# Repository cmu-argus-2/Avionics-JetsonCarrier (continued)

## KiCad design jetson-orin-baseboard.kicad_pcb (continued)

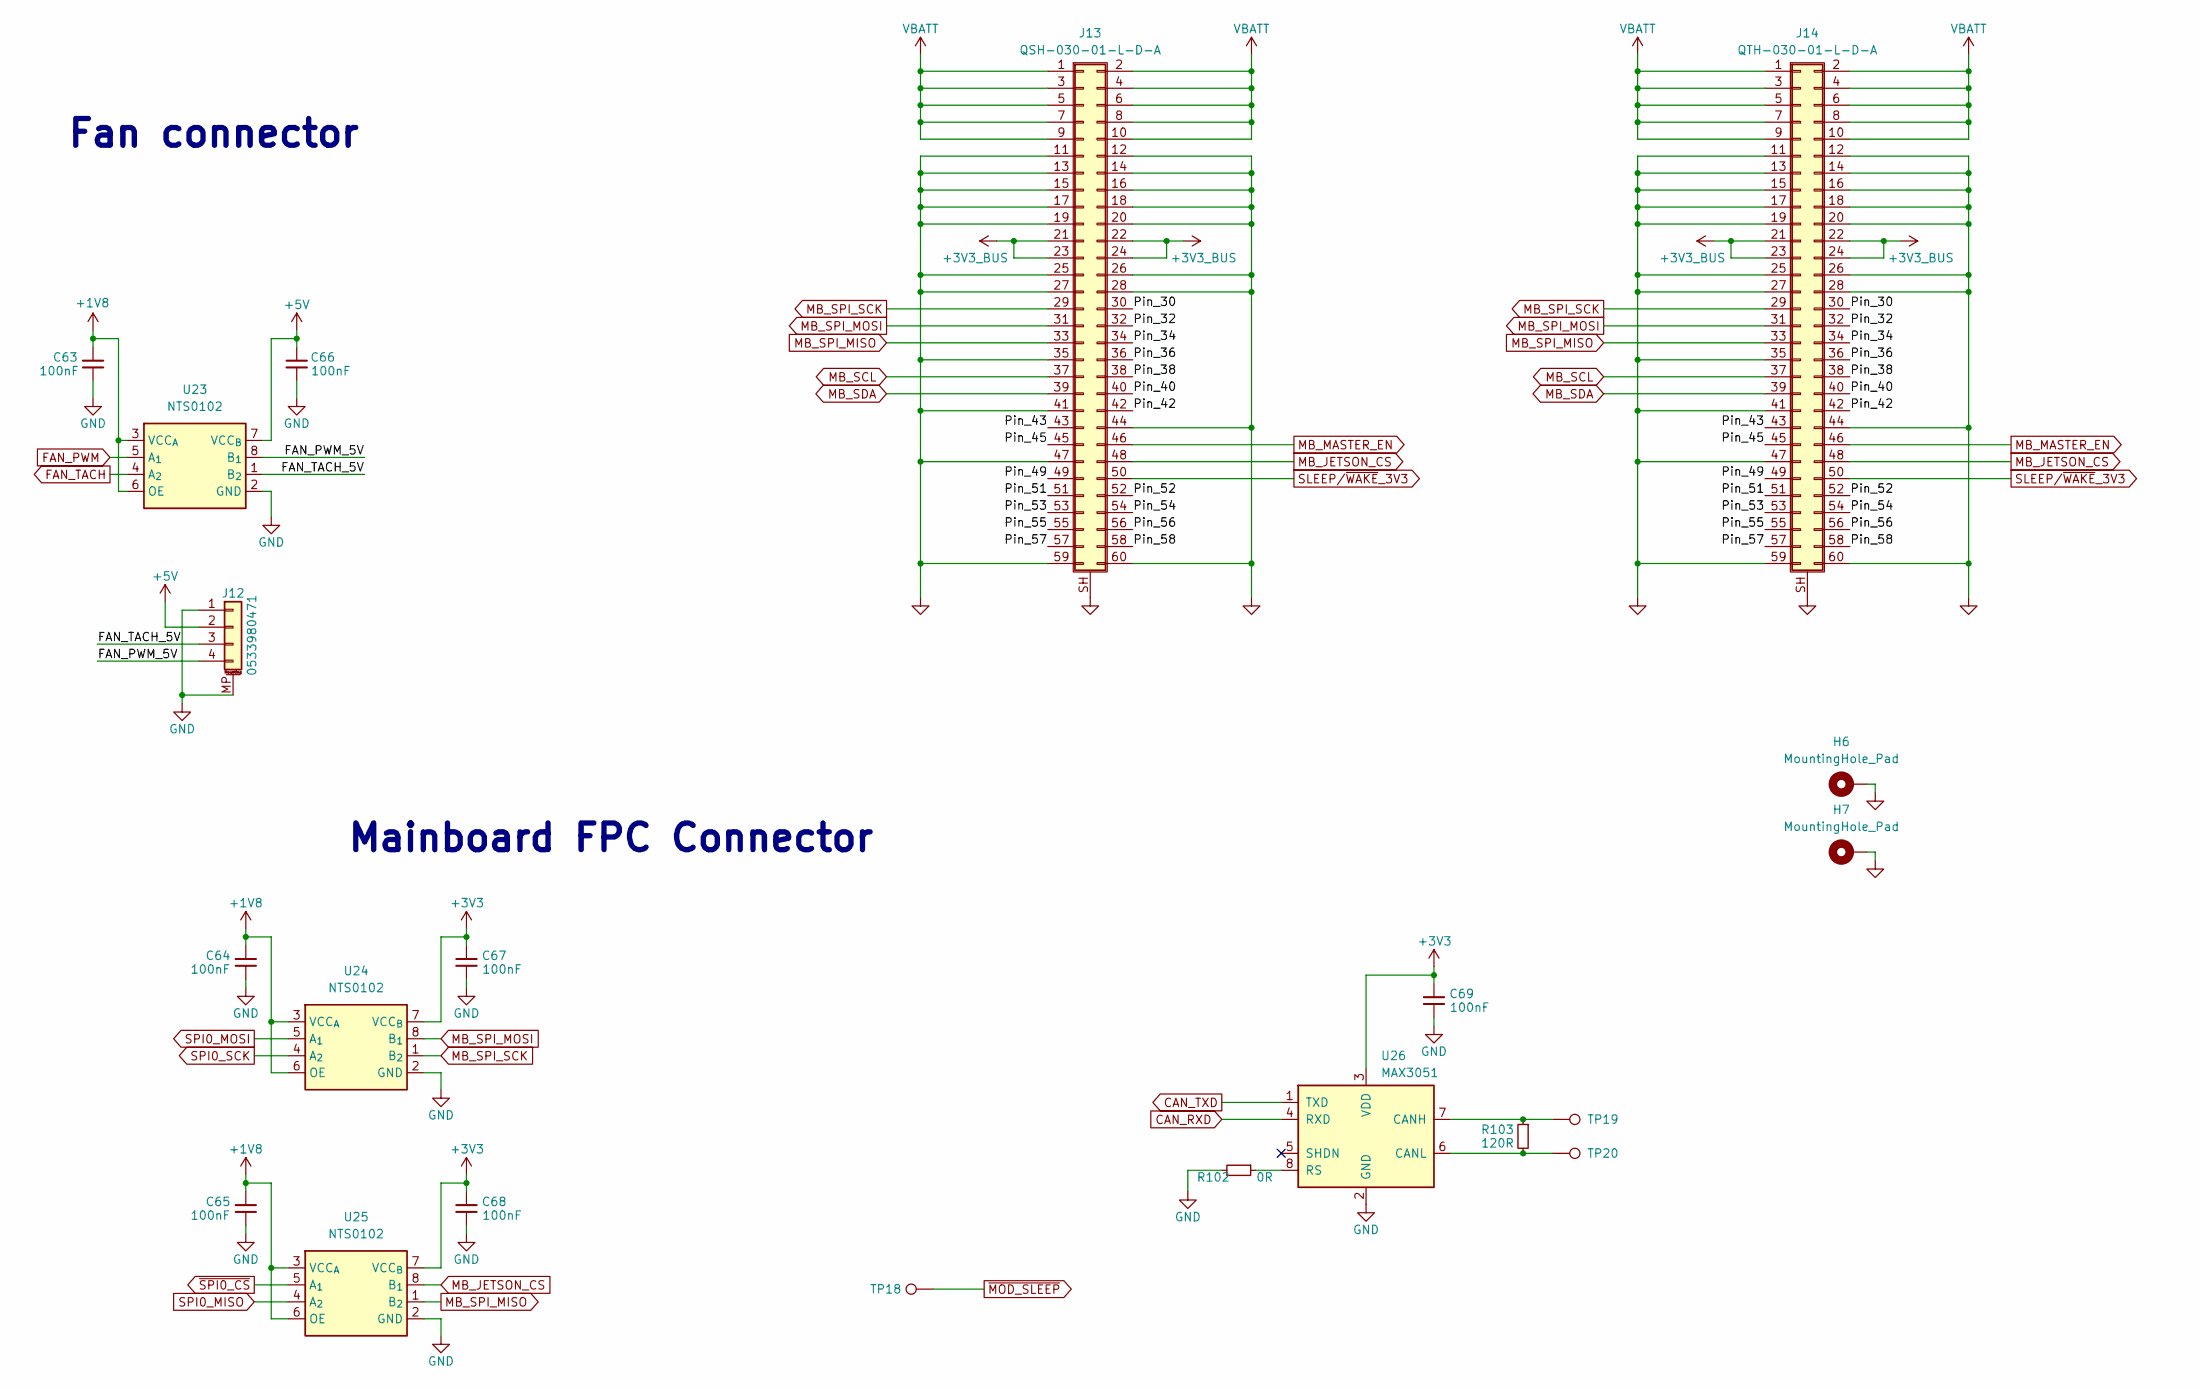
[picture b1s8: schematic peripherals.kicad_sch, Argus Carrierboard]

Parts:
C63, C64, C65, C66, C67, C68, C69: 100nF; C_0603_1608Metric; MPN C307348; LCSC C14663
H6, H7: MountingHole_Pad; MountingHole_2.5mm_Pad_Via
J12: 0533980471; Molex_PicoBlade_53398-0471_1x04-1MP_P1.25mm_Vertical; MPN C225106; LCSC C17617036
J13: QSH-030-01-L-D-A; SAMTEC_QSH-030-01-L-D-A; LCSC C2909821
J14: QTH-030-01-L-D-A; SAMTEC-QTH-030-01-X-D-A; LCSC C2843756
R102: 0R; R_0603_1608Metric; MPN C190119; LCSC C21189
R103: 120R; R_0603_1608Metric; MPN C71617; LCSC C22787
TP18, TP19, TP20: TP_0.75mm_SMD; TestPoint_Pad_D1.0mm
U23, U24, U25: NTS0102; NXP_XSON-8; MPN NTS0102GT; LCSC C2687851
U26: MAX3051; SOT-23-8; LCSC C112005

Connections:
+1V8: C63.1, C64.1, C65.1, U23.3 (VCC_{A}), U23.6 (OE), U24.3 (VCC_{A}), U24.6 (OE), U25.3 (VCC_{A}), U25.6 (OE); also elsewhere on the board
+3V3: C67.1, C68.1, C69.1, U24.7 (VCC_{B}), U25.7 (VCC_{B}), U26.3 (VDD); also elsewhere on the board
+3V3_BUS: J13.21, J13.22, J13.23, J13.24, J14.21, J14.22, J14.23, J14.24; also elsewhere on the board
+5V: C66.1, J12.2, U23.7 (VCC_{B}); also elsewhere on the board
/Peripherals/FAN_PWM_5V: J12.4, U23.8 (B_{1})
/Peripherals/FAN_TACH_5V: J12.3, U23.1 (B_{2})
/Peripherals/Pin_30: J13.30, J14.30
/Peripherals/Pin_32: J13.32, J14.32
/Peripherals/Pin_34: J13.34, J14.34
/Peripherals/Pin_36: J13.36, J14.36
/Peripherals/Pin_38: J13.38, J14.38
/Peripherals/Pin_40: J13.40, J14.40
/Peripherals/Pin_42: J13.42, J14.42
/Peripherals/Pin_43: J13.43, J14.43
/Peripherals/Pin_45: J13.45, J14.45
/Peripherals/Pin_49: J13.49, J14.49
/Peripherals/Pin_51: J13.51, J14.51
/Peripherals/Pin_52: J13.52, J14.52
/Peripherals/Pin_53: J13.53, J14.53
/Peripherals/Pin_54: J13.54, J14.54
/Peripherals/Pin_55: J13.55, J14.55
/Peripherals/Pin_56: J13.56, J14.56
/Peripherals/Pin_57: J13.57, J14.57
/Peripherals/Pin_58: J13.58, J14.58
CAN_RXD: U26.4 (RXD); also elsewhere on the board
CAN_TXD: U26.1 (TXD); also elsewhere on the board
FAN_PWM: U23.5 (A_{1}); also elsewhere on the board
FAN_TACH: U23.4 (A_{2}); also elsewhere on the board
GND: C63.2, C64.2, C65.2, C66.2, C67.2, C68.2, C69.2, H6.1 (1_1), H7.1 (1_1), J12.1, J12.MP (MountPin), J13.11, J13.12, J13.13, J13.14, J13.15, J13.16, J13.17, J13.18, J13.19, J13.20, J13.25, J13.26, J13.27, J13.28, J13.35, J13.41, J13.44, J13.47, J13.59, J13.60, J13.SH (Shield), J14.11, J14.12, J14.13, J14.14, J14.15, J14.16, J14.17, J14.18, J14.19, J14.20, J14.25, J14.26, J14.27, J14.28, J14.35, J14.41, J14.44, J14.47, J14.59, J14.60, J14.SH (Shield), R102.2, U23.2 (GND), U24.2 (GND), U25.2 (GND), U26.2 (GND); also elsewhere on the board
MB_JETSON_CS: J13.48, J14.48, U25.8 (B_{1})
MB_MASTER_EN: J13.46, J14.46; also elsewhere on the board
MB_SCL: J13.37, J14.37; also elsewhere on the board
MB_SDA: J13.39, J14.39; also elsewhere on the board
MB_SPI_MISO: J13.33, J14.33, U25.1 (B_{2})
MB_SPI_MOSI: J13.31, J14.31, U24.8 (B_{1})
MB_SPI_SCK: J13.29, J14.29, U24.1 (B_{2})
unnamed: R103.1, TP19.1 (1_1), U26.7 (CANH)
unnamed: R103.2, TP20.1 (1_1), U26.6 (CANL)
unnamed: R102.1, U26.8 (RS)
SLEEP/~WAKE_3V3: J13.50, J14.50; also elsewhere on the board
SPI0_MISO: U25.4 (A_{2}); also elsewhere on the board
SPI0_MOSI: U24.5 (A_{1}); also elsewhere on the board
SPI0_SCK: U24.4 (A_{2}); also elsewhere on the board
VBATT: J13.1, J13.2, J13.3, J13.4, J13.5, J13.6, J13.7, J13.8, J13.9, J13.10, J14.1, J14.2, J14.3, J14.4, J14.5, J14.6, J14.7, J14.8, J14.9, J14.10; also elsewhere on the board
~MOD_SLEEP: TP18.1 (1_1); also elsewhere on the board
~SPI0_CS: U25.5 (A_{1}); also elsewhere on the board

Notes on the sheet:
Fan connector
Mainboard FPC Connector

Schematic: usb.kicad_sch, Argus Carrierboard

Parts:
C23, C25: 10uF; C_0603_1608Metric; MPN C697423; LCSC C96446
C24, C26, C27, C31: 100nF; C_0603_1608Metric; MPN C307348; LCSC C14663
C28, C30: 47pF; C_0402_1005Metric; MPN C126511; LCSC C1567
C29: 1uF; C_0603_1608Metric; MPN C2214844; LCSC C15849
D4, D5: LED_G_0603_LTST-C190GKT; LED_0603_1608Metric; MPN C2909774; LCSC C2290
D6: LED_G_0603_LTST-C190GKT; LED_0603_1608Metric; MPN C2909774; LCSC C12065
D7: ESD9X5.0ST5G; D_SOD-923; MPN C87910; LCSC C87910
J3: USB_C_Receptacle_USB2.0_16P; USB_C_Receptacle_GCT_USB4105-xx-A_16P_TopMnt_Horizontal; LCSC C3020560
R22: 10k; R_0603_1608Metric; MPN C2479067; LCSC C25804
R23, R24: 0R; R_0402_1005Metric; MPN C190119; LCSC C17168
R25, R26: 3k3; R_0603_1608Metric; MPN C844928; LCSC C22978
R27: 4k7; R_0603_1608Metric; MPN C844931; LCSC C23162
R28, R29: 27R; R_0603_1608Metric; MPN C844545; LCSC C227752
R30, R31: 5k1; R_0603_1608Metric; MPN C490833; LCSC C23186
TP6, TP7: TP_0.75mm_SMD; TestPoint_Pad_D1.0mm
U2: NCP730BMT330; WSON-6-1EP_2x2mm_P0.65mm; MPN C892821; LCSC C892821
U3: FT230X; QFN-16-1EP_4x4mm_P0.65mm_EP2.1x2.1mm; MPN C128629; LCSC C128629
U4: TPD4E05U06QDQARQ1; USON-10_TEX; MPN C81353; LCSC C81353

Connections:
/Debug/FTDI_3V3: C23.2, C24.2, C26.2, R22.2, R25.2, R26.1, U2.1 (V_{OUT}), U3.1 (V_{CCIO}), U3.8 (3V3_{OUT}), U3.10 (V_{CC})
/Debug/FTDI_CBUS0: TP6.1 (1_1), U3.12 (CBUS0)
/Debug/FTDI_CBUS3: TP7.1 (1_1), U3.14 (CBUS3)
/Debug/FTDI_LED_RX: D4.1 (K), U3.11 (CBUS1)
/Debug/FTDI_LED_TX: D5.1 (K), U3.5 (CBUS2)
/Debug/USBC3_CC1: J3.A5 (CC1), R30.1, U4.4, U4.7
/Debug/USBC3_CC2: J3.B5 (CC2), R31.1, U4.5, U4.6
/Debug/USBC3_D_N: C28.1, J3.A7 (D-), J3.B7 (D-), R28.1, U4.1, U4.10
/Debug/USBC3_D_P: C30.2, J3.A6 (D+), J3.B6 (D+), R29.1, U4.2, U4.9
/Debug/USBC3_VBUS: C25.2, C29.2, C31.2, D7.1 (K), J3.A4 (VBUS), J3.A9 (VBUS), J3.B4 (VBUS), J3.B9 (VBUS), R27.1, U2.4 (EN), U2.6 (V_{IN})
/Debug/USB_FTDI_N: R28.2, U3.7 (D-)
/Debug/USB_FTDI_P: R29.2, U3.6 (D+)
DEBUG_RXD: R23.2; also elsewhere on the board
DEBUG_TXD: R24.2; also elsewhere on the board
GND: C23.1, C24.1, C25.1, C26.1, C27.2, C28.2, C29.1, C30.1, C31.1, D6.1 (K), D7.2 (A), J3.A1 (GND), J3.A12 (GND), J3.B1 (GND), J3.B12 (GND), J3.SH (SHIELD), R30.2, R31.2, U2.3 (GND), U2.5 (PG), U2.7 (GND), U3.3 (GND), U3.13 (GND), U3.17 (GND), U4.3, U4.8; also elsewhere on the board
unnamed: D4.2 (A), R25.1
unnamed: D5.2 (A), R26.2
unnamed: D6.2 (A), R27.2
unnamed: R24.1, U3.2 (RXD)
unnamed: R23.1, U3.15 (TXD)
unnamed: C27.1, R22.1, U3.9 (~RESET)

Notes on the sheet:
USBC3
USB-UART Bridge
Debug USB-C 3

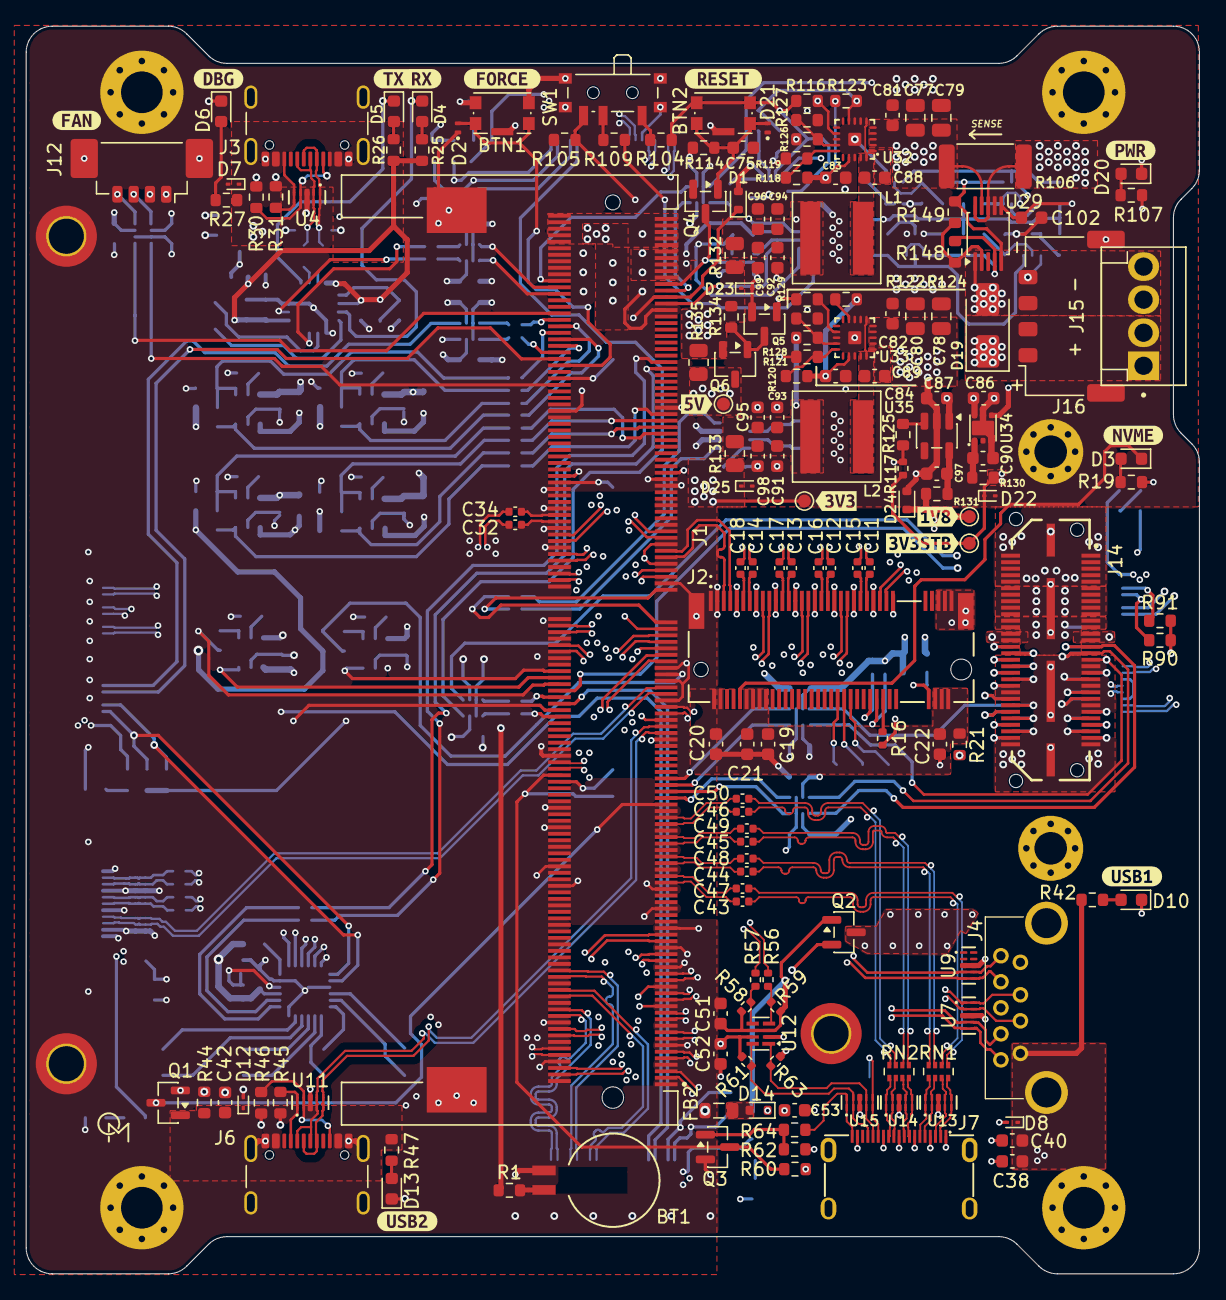
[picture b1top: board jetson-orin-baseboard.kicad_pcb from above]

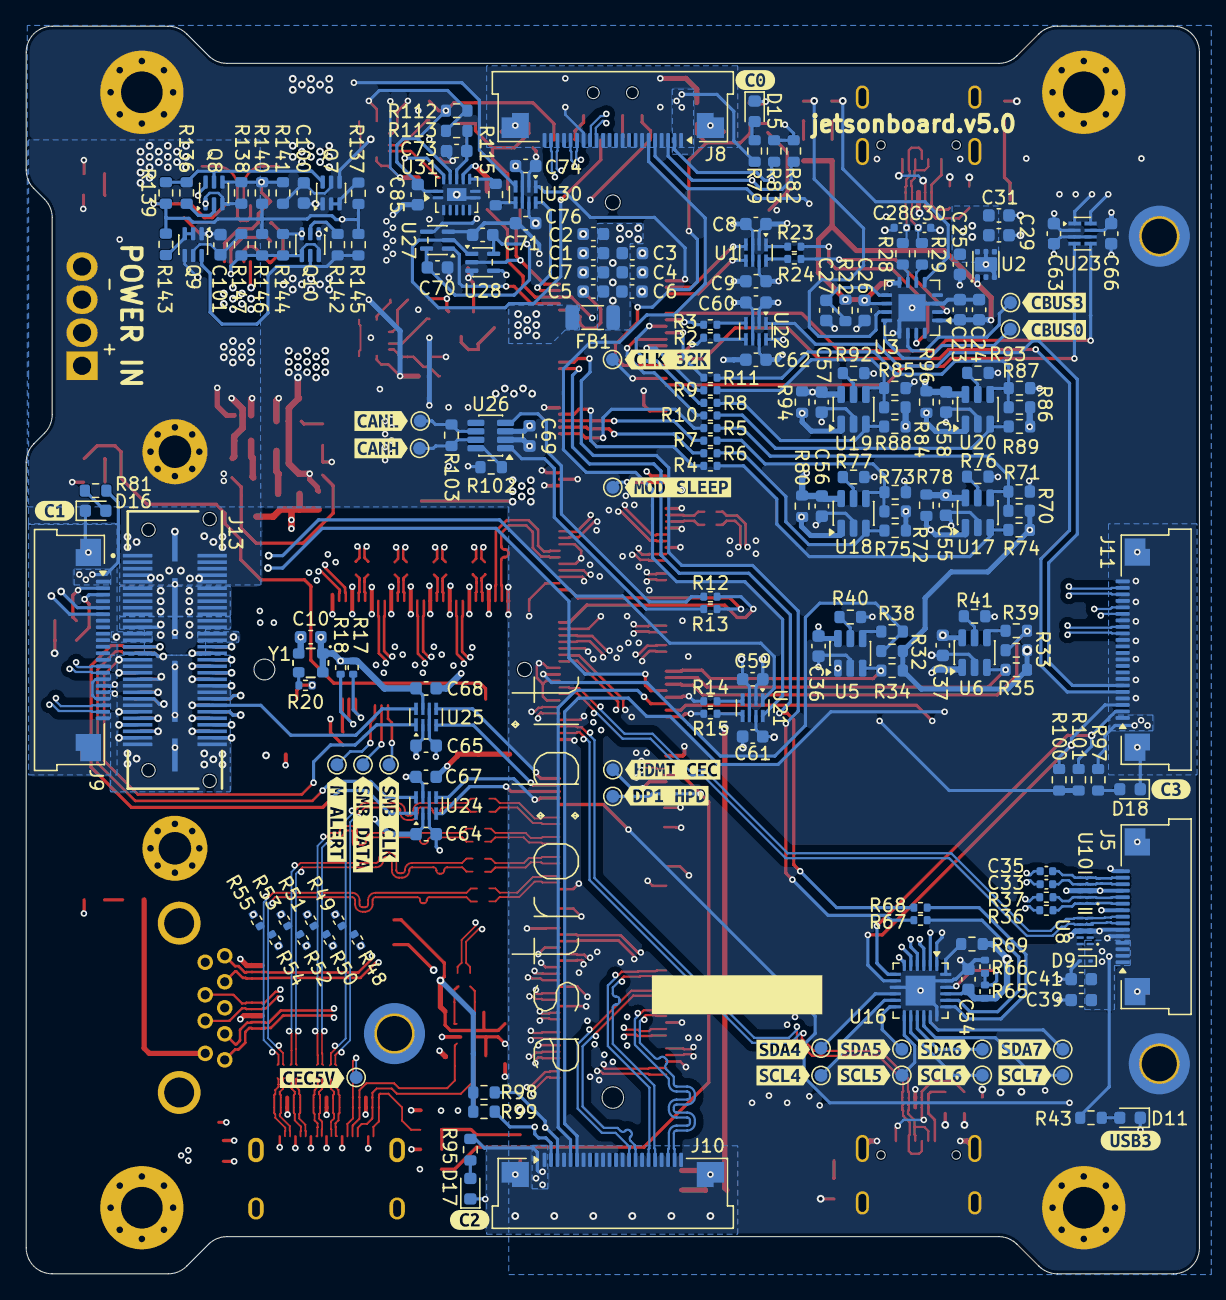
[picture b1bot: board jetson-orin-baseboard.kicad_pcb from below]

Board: 8 copper layers, 90.2 x 95.9 mm, 414 parts (227 on the bottom side), 325 nets.

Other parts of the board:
C100, C101: 10n; C_0603_1608Metric
Q7, Q9: NX3008NBKS; SOT-363_SC-70-6
Q8, Q10: MBT2222ADW1T1; SOT-363_SC-70-6
R136, R142: 680R; R_0603_1608Metric
R137, R143: 100k; R_0603_1608Metric
R138, R144: 0R; R_0603_1608Metric
R139, R140, R145, R146: 10k; R_0603_1608Metric
R141, R147: 200k; R_0603_1608Metric
kibuzzard-6AA4CB0A: G***; kibuzzard-6AA4CB0A
kibuzzard-6AA4CB7C: G***; kibuzzard-6AA4CB7C
kibuzzard-6AA4CB93: G***; kibuzzard-6AA4CB93
kibuzzard-6AA4CBA6: G***; kibuzzard-6AA4CBA6
kibuzzard-6AA4CCDD: G***; kibuzzard-6AA4CCDD
kibuzzard-6AA4CCE8: G***; kibuzzard-6AA4CCE8
kibuzzard-6AA4CCF3: G***; kibuzzard-6AA4CCF3
kibuzzard-6AA4CCFD: G***; kibuzzard-6AA4CCFD
kibuzzard-6AA4D0D5: G***; kibuzzard-6AA4D0D5
kibuzzard-6AA4D0E1: G***; kibuzzard-6AA4D0E1
kibuzzard-6AA4D3A3: G***; kibuzzard-6AA4D3A3
kibuzzard-6AA4D3AB: G***; kibuzzard-6AA4D3AB
kibuzzard-6AA4D4B3: G***; kibuzzard-6AA4D4B3
kibuzzard-6AA4D4C2: G***; kibuzzard-6AA4D4C2
kibuzzard-6AA4D4DE: G***; kibuzzard-6AA4D4DE
kibuzzard-6AA4D12B: G***; kibuzzard-6AA4D12B
kibuzzard-6AA4D056: G***; kibuzzard-6AA4D056
kibuzzard-6AA5BAD4: G***; kibuzzard-6AA5BAD4
kibuzzard-6AA5C51C: G***; kibuzzard-6AA5C51C
kibuzzard-6AA5EB39: G***; kibuzzard-6AA5EB39
kibuzzard-6AA5EB57: G***; kibuzzard-6AA5EB57
kibuzzard-6AA5EC14: G***; kibuzzard-6AA5EC14
kibuzzard-6AA5EC48: G***; kibuzzard-6AA5EC48
kibuzzard-6AA615B2: G***; kibuzzard-6AA615B2
kibuzzard-6AA616B5: G***; kibuzzard-6AA616B5
kibuzzard-6AA622B3: G***; kibuzzard-6AA622B3
kibuzzard-6AA6154A: G***; kibuzzard-6AA6154A
kibuzzard-6AA6159C: G***; kibuzzard-6AA6159C
kibuzzard-6AB55D8A: G***; kibuzzard-6AB55D8A
kibuzzard-6AB55D85: G***; kibuzzard-6AB55D85
kibuzzard-6ABE9DBB: G***; kibuzzard-6ABE9DBB
kibuzzard-6ABE9DD8: G***; kibuzzard-6ABE9DD8
kibuzzard-6ABE9DF7: G***; kibuzzard-6ABE9DF7
kibuzzard-6ABE9E40: G***; kibuzzard-6ABE9E40
kibuzzard-6ABE9EA3: G***; kibuzzard-6ABE9EA3
kibuzzard-6ABE9EB3: G***; kibuzzard-6ABE9EB3
kibuzzard-6ABE9F12: G***; kibuzzard-6ABE9F12
kibuzzard-6ABE9F28: G***; kibuzzard-6ABE9F28
kibuzzard-6ABEA036: G***; kibuzzard-6ABEA036

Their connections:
+3V3_BUS: R137.1, R139.1, R140.1, R143.1, R145.1, R146.1; also elsewhere on the board
/Supply/ISENSE_SCL: Q8.4 (E2), Q8.6 (C1), R138.1, R140.2, R141.1; also elsewhere on the board
/Supply/ISENSE_SDA: Q10.4 (E2), Q10.6 (C1), R144.1, R146.2, R147.1; also elsewhere on the board
GND: C100.2, C101.2, Q7.1 (S2), Q7.4 (S1), Q9.1 (S2), Q9.4 (S1); also elsewhere on the board
MB_SCL: Q8.1 (E1), Q8.3 (C2), R138.2; also elsewhere on the board
MB_SDA: Q10.1 (E1), Q10.3 (C2), R144.2; also elsewhere on the board
unnamed: Q7.6 (D1), Q8.5 (B2), R136.2, R139.2
unnamed: Q7.2 (G2), Q7.3 (D2), R137.2
unnamed: C100.1, Q7.5 (G1), R141.2
unnamed: Q8.2 (B1), R136.1
unnamed: Q9.2 (G2), Q9.3 (D2), R143.2
unnamed: C101.1, Q9.5 (G1), R147.2
unnamed: Q10.2 (B1), R142.1
unnamed: Q9.6 (D1), Q10.5 (B2), R142.2, R145.2
